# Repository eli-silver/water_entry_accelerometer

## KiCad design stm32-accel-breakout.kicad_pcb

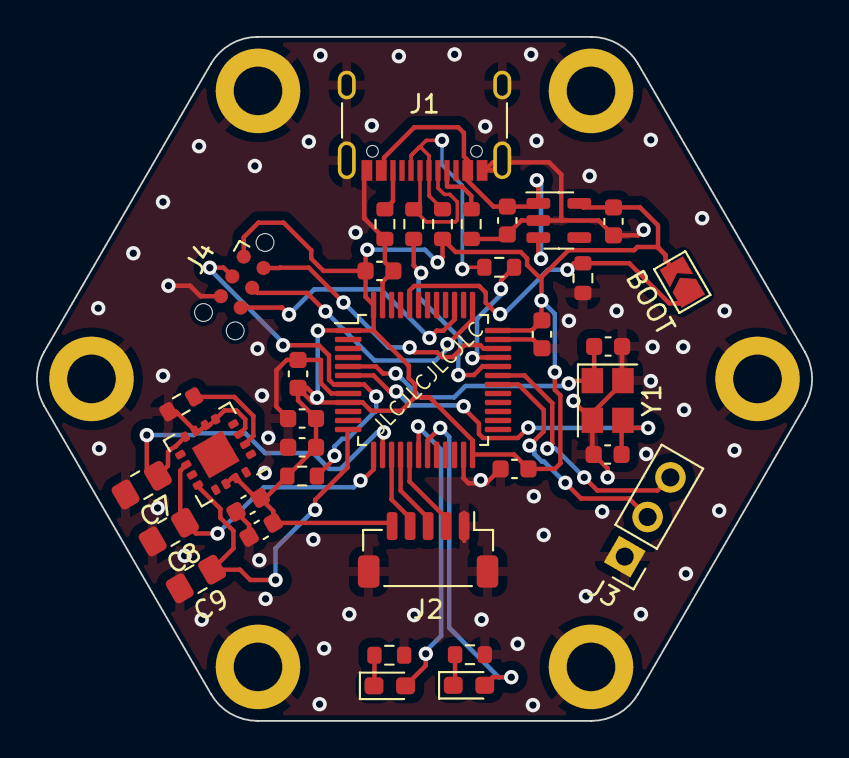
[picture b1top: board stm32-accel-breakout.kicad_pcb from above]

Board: 2 copper layers, 43.1 x 38.0 mm, 42 parts (0 on the bottom side), 29 nets.

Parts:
C1, C2: 10uF; C_0603_1608Metric
C3, C4, C5, C6, C10: 0.1uF; C_0603_1608Metric
C7, C8, C9: 4.7nF; C_0805_2012Metric_Pad1.18x1.45mm_HandSolder
C11, C12: 1uF; C_0603_1608Metric
C13: 10nF; C_0603_1608Metric
C14, C15: 20pF; C_0603_1608Metric
D1, D2: LED; LED_0603_1608Metric_Pad1.05x0.95mm_HandSolder
H1, H2, H3, H4, H5, H6: MountingHole_Pad; MountingHole_2.7mm_M2.5_DIN965_Pad
J1: USB_C_Receptacle_USB2.0; USB_C_Receptacle_XKB_U262-16XN-4BVC11
J2: JST-SH-01x05; JST_SH_BM05B-SRSS-TB_1x05-1MP_P1.00mm_Vertical
J3: Conn_01x03; PinHeader_1x03_P2.54mm_Vertical
J4: Conn_ARM_SWD_TagConnect_TC2030-NL; Tag-Connect_TC2030-IDC-NL_2x03_P1.27mm_Vertical
JP1: Jumper_2_Open; SolderJumper-2_P1.3mm_Open_TrianglePad1.0x1.5mm
R1, R2: 5.1k; R_0603_1608Metric
R3: 100k; R_0603_1608Metric
R4: 1.5k; R_0603_1608Metric
R5, R6: 22; R_0603_1608Metric
R7, R8: 10k; R_0603_1608Metric
R9, R10: 1k; R_0603_1608Metric
U1: STM32F103C8Tx; LQFP-48_7x7mm_P0.5mm
U2: AP2112K-3.3; SOT-23-5
U3: ADXL335; LGA-16_4x4mm_P0.65mm_LayoutBorder4x4y_EP
Y1: Crystal_GND24; Crystal_SMD_3225-4Pin_3.2x2.5mm

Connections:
+3.3V: C1.2, C3.1, C4.1, C5.1, C6.1, C10.1, C11.1, C12.1, C13.1, J2.5, J4.1 (VCC), JP1.2 (B), R4.2, R7.2, U1.1 (VBAT), U1.9 (VDDA), U1.24 (VDD), U1.36 (VDD), U1.48 (VDD), U2.5 (VOUT), U3.14 (V_s), U3.15 (V_s)
+5V: C2.2, J1.A4 (VBUS), J1.A9 (VBUS), J1.B4 (VBUS), J1.B9 (VBUS), U2.1 (VIN), U2.3 (EN)
ADXL_SELF_TEST: R8.2, U3.2 (ST)
ADXL_X1_{out}: C9.1, U1.12 (PA2), U3.12 (X_out)
ADXL_X2_{out}: J2.4, U1.15 (PA5)
ADXL_Y1_{out}: C8.1, U1.13 (PA3), U3.10 (Y_out)
ADXL_Y2_{out}: J2.3, U1.16 (PA6)
ADXL_Z1_{out}: C7.1, U1.14 (PA4), U3.8 (Z_out)
ADXL_Z2_{out}: J2.2, U1.17 (PA7)
BOOT0: JP1.1 (A), R3.1, U1.44 (BOOT0)
GND: C1.1, C2.1, C3.2, C4.2, C5.2, C6.2, C7.2, C8.2, C9.2, C10.2, C11.2, C12.2, C13.2, C14.2, C15.2, H1.1, H2.1, H3.1, H4.1, H5.1, H6.1, J1.A1 (GND), J1.A12 (GND), J1.B1 (GND), J1.B12 (GND), J1.S1 (SHIELD), J2.1, J2.MP (MountPin), J3.1, J4.5 (GND), R1.2, R2.2, R3.2, R8.1, R9.1, R10.1, U1.8 (VSSA), U1.23 (VSS), U1.35 (VSS), U1.47 (VSS), U2.2 (GND), U3.3 (COM), U3.5 (COM), U3.6 (COM), U3.7 (COM), Y1.2, Y1.4
unnamed: D1.2 (A), U1.18 (PB0)
unnamed: D1.1 (K), R9.2
unnamed: D2.2 (A), U1.19 (PB1)
unnamed: D2.1 (K), R10.2
unnamed: J1.A5 (CC1), R1.1
unnamed: J1.B5 (CC2), R2.1
unnamed: R6.1, U1.32 (PA11)
unnamed: R5.1, U1.33 (PA12)
unnamed: C14.1, U1.5 (PD0), Y1.1
unnamed: C15.1, U1.6 (PD1), Y1.3
RST: J4.3 (~RESET), R7.1, U1.7 (NRST)
RX1: J3.3, U1.31 (PA10)
SWCLK: J4.4 (SWCLK), U1.37 (PA14)
SWDIO: J4.2 (SWDIO), U1.34 (PA13)
SWO: J4.6 (SWO), U1.39 (PB3)
TX1: J3.2, U1.30 (PA9)
USB_D+: J1.A6 (D+), J1.B6 (D+), R4.1, R5.2
USB_D-: J1.A7 (D-), J1.B7 (D-), R6.2

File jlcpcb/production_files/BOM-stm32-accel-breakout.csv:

Comment,Designator,Footprint,LCSC
Crystal_GND24,Y1,Crystal_SMD_3225-4Pin_3.2x2.5mm,C13738
0.1uF,"C10,C3,C4,C5,C6",C_0603_1608Metric,C14663
1uF,"C11,C12",C_0603_1608Metric,C15849
JST-SH-01x05,J2,JST_SH_BM05B-SRSS-TB_1x05-1MP_P1.00mm_Vertical,C160391
20pF,"C14,C15",C_0603_1608Metric,C1648
4.7nF,"C7,C8,C9",C_0805_2012Metric_Pad1.18x1.45mm_HandSolder,C1744
10uF,"C1,C2",C_0603_1608Metric,C19702
1k,"R10,R9",R_0603_1608Metric,C21190
1.5k,R4,R_0603_1608Metric,C22843
LED,D2,LED_0603_1608Metric_Pad1.05x0.95mm_HandSolder,C2286
5.1k,"R1,R2",R_0603_1608Metric,C23186
22,"R5,R6",R_0603_1608Metric,C23345
100k,R3,R_0603_1608Metric,C25803
10k,"R7,R8",R_0603_1608Metric,C25804
USB_C_Receptacle_USB2.0,J1,USB_C_Receptacle_XKB_U262-16XN-4BVC11,C319148
ADXL335,U3,LGA-16_4x4mm_P0.65mm_LayoutBorder4x4y_EP,C34439
AP2112K-3.3,U2,SOT-23-5,C51118
10nF,C13,C_0603_1608Metric,C57112
LED,D1,LED_0603_1608Metric_Pad1.05x0.95mm_HandSolder,C72041
STM32F103C8Tx,U1,LQFP-48_7x7mm_P0.5mm,C8734

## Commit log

2023-12-06 minor edits to the routing
2023-12-06 changed programming header to tag connect
2023-12-06 changed connector for breakout accelerometer to jst-sh
2023-12-11 final edits before sending PCBs for fabrication. 10 boards ordered from JLCPCB
2023-12-20 stm32 project git version control attempt
